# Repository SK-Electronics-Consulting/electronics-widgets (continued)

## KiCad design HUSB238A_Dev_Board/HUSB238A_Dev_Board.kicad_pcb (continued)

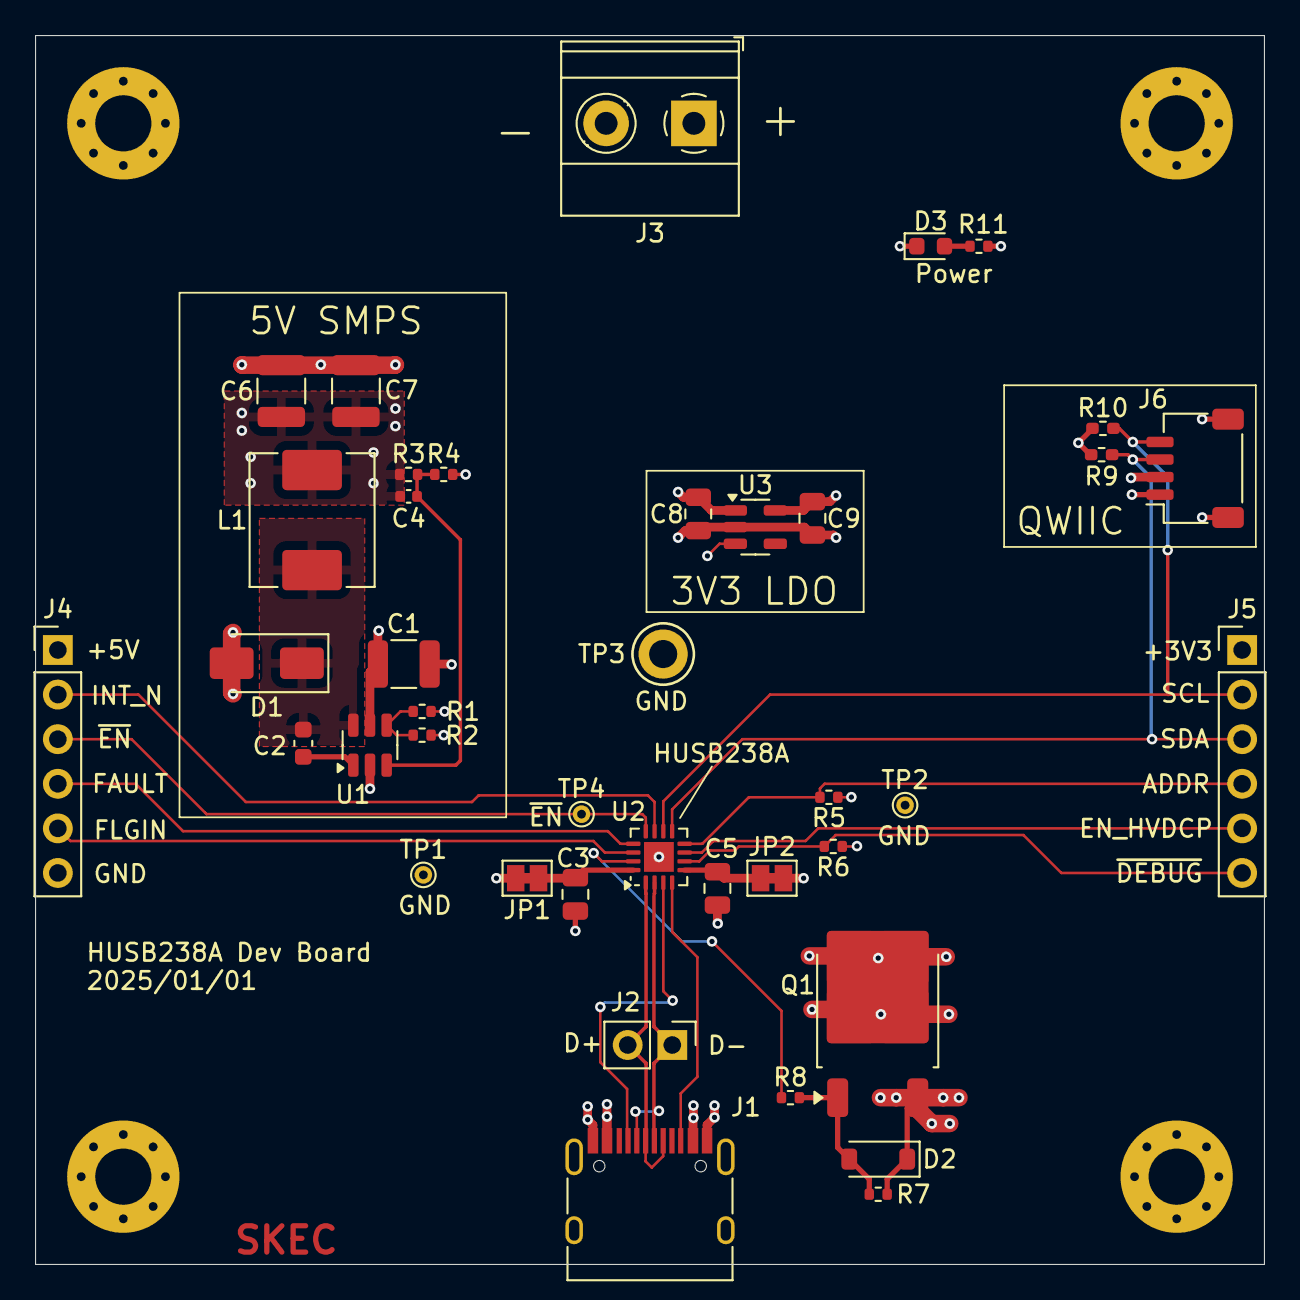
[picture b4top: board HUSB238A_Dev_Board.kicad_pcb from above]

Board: 4 copper layers, 70.0 x 70.0 mm, 44 parts (0 on the bottom side), 27 nets.

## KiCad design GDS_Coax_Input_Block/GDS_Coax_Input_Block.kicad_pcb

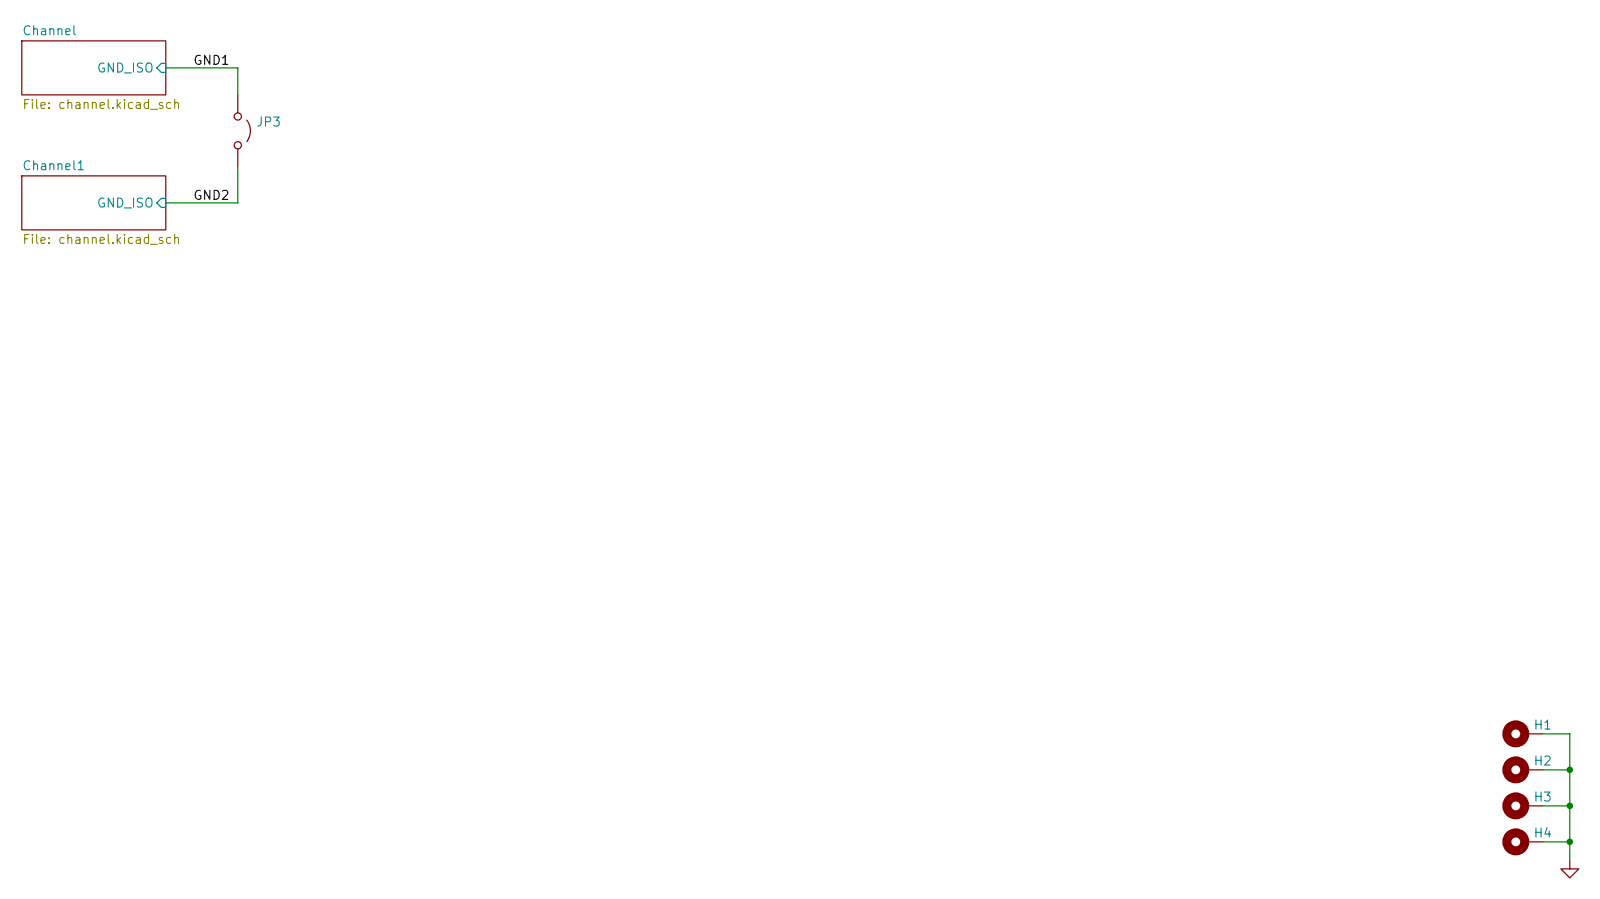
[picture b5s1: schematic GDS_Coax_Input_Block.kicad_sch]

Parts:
H1, H2, H3, H4: MountingHole_Pad; MountingHole_3.2mm_M3_Pad_Via
JP3: Jumper_2_Open; PinHeader_1x02_P2.54mm_Vertical

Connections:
/GND1: JP3.1 (A); also elsewhere on the board
/GND2: JP3.2 (B); also elsewhere on the board
GND: H1.1, H2.1, H3.1, H4.1

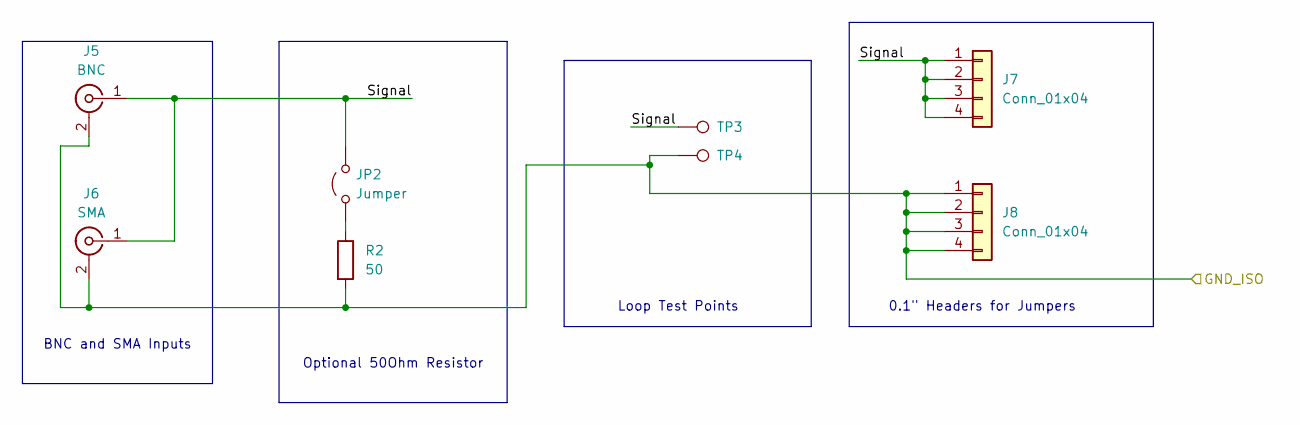
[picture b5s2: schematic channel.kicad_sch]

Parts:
J5: BNC; BNC_TEConnectivity_1478204_Vertical
J6: SMA; SMA_Amphenol_132134-11_Vertical
J7, J8: Conn_01x04; PinHeader_1x04_P2.54mm_Vertical
JP2: Jumper; SolderJumper-2_P2.54mm_Bridged
R2: 50; R_0603_1608Metric_Pad0.98x0.95mm_HandSolder
TP3, TP4: TestPoint; TestPoint_Keystone_5010-5014_Multipurpose

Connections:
/Channel/Signal: J5.1 (In), J6.1 (In), J7.1, J7.2, J7.3, J7.4, JP2.2 (B), TP3.1
/GND1: J5.2 (Ext), J6.2 (Ext), J8.1, J8.2, J8.3, J8.4, R2.2, TP4.1; also elsewhere on the board
unnamed: JP2.1 (A), R2.1

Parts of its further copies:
J1: BNC; BNC_TEConnectivity_1478204_Vertical
J2: SMA; SMA_Amphenol_132134-11_Vertical
J3, J4: Conn_01x04; PinHeader_1x04_P2.54mm_Vertical
JP1: Jumper; SolderJumper-2_P2.54mm_Bridged
R1: 50; R_0603_1608Metric_Pad0.98x0.95mm_HandSolder
TP1, TP2: TestPoint; TestPoint_Keystone_5010-5014_Multipurpose

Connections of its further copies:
/Channel1/Signal: J1.1 (In), J2.1 (In), J3.1, J3.2, J3.3, J3.4, JP1.2 (B), TP1.1
/GND2: J1.2 (Ext), J2.2 (Ext), J4.1, J4.2, J4.3, J4.4, R1.2, TP2.1; also elsewhere on the board
unnamed: JP1.1 (A), R1.1

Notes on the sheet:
Loop Test Points
BNC and SMA Inputs
0.1" Headers for Jumpers
Optional 50Ohm Resistor

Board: 4 copper layers, 21 parts (0 on the bottom side), 7 nets, no tracks yet.

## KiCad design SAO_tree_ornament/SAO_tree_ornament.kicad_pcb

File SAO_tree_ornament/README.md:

# SAO Tree Ornament

This board allows you to easily hang and display your SAOs on a tree or other decoration.  It provides power via USB-PB and optionally a small MCU to drive the pins.

## Features

* USB-PD Power entry.  Negotiates for up to <20V@3.25A> (The USB-PD 3.0 65W profile).
* Distributes the high voltage out to other ornaments
* Converts the high voltage down to 3.3V for the SAO
* An MCU can drive the I2C and the GPIO pins if the SAO needs it.

## TODO

* Test and characterize the current capability of the buck converter

## Next Version Notes

1. Add SOME LEDs to the front of the board to optionally backlight the SAO
2. Add some art to the front of the board
3. Figure out a more efficient counterbalance solution. I underestimated the weight of some of the SAO. A 5mm dowel to bind to the branch might be an option.
4. Might need to move the 2-pin connectors so they don't interfere with the SAO connector.  TBD
5. Reduce 6-pin connector hole sizes. A 0.2mm diameter drop is a good start.  Probably will end up at 0.3mm reduction overall.

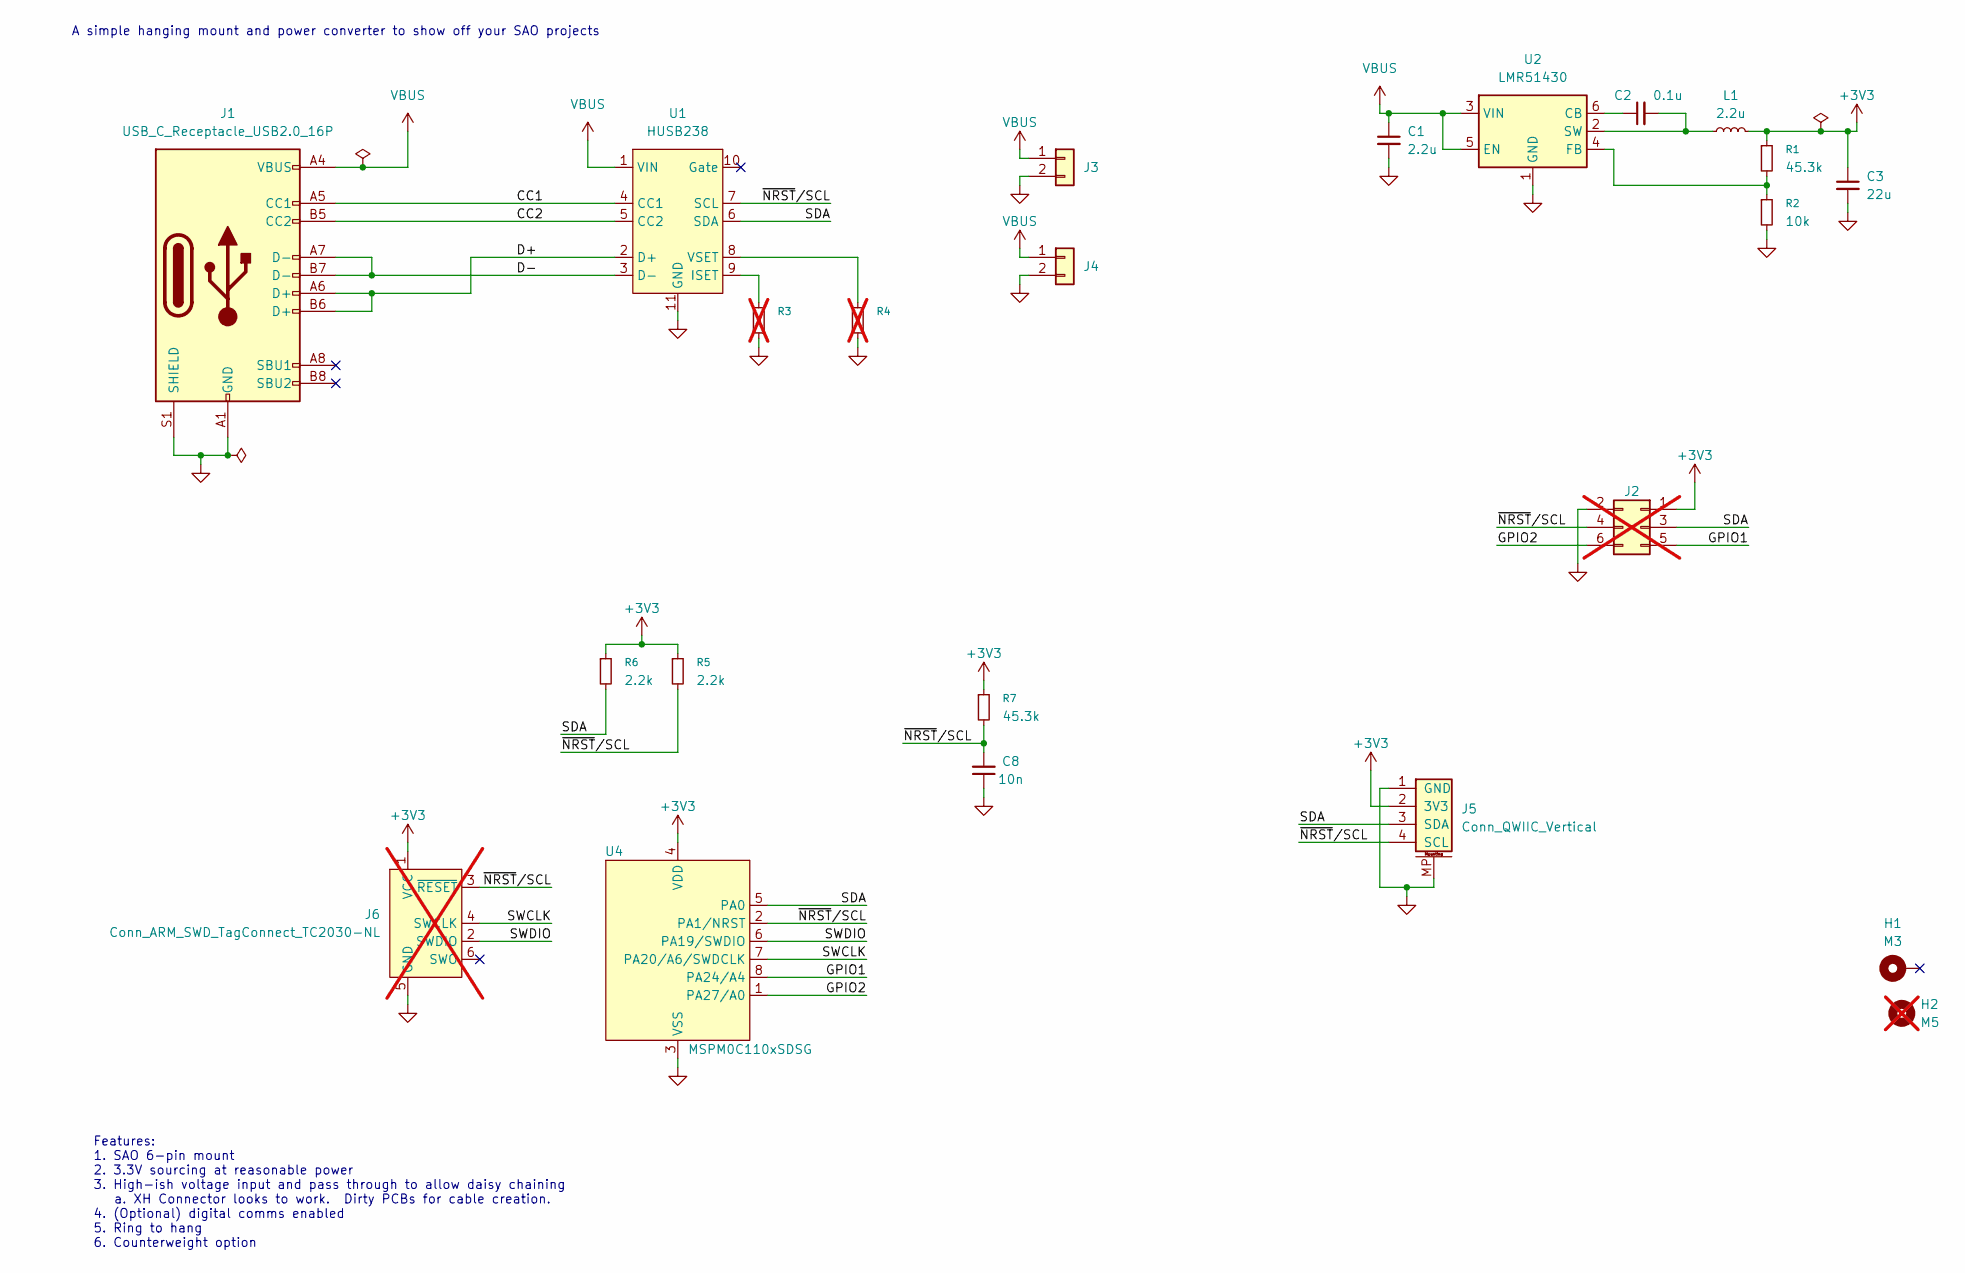
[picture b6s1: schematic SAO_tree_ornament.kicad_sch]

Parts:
C1: 2.2u; C_0603_1608Metric; MPN CL10A225KB8NNNC; JLCPCB Part No. C913904
C2: 0.1u; C_0402_1005Metric; MPN CC0402KRX5R9BB104; JLCPCB Part No. C105882
C3: 22u; C_0603_1608Metric; MPN CL10A226MO7JZNC; JLCPCB Part No. C2762594
C8: 10n; C_0402_1005Metric; MPN CC0402KRX7R0BB103; JLCPCB Part No. C527014
H1: M3; Nut_M3_Sinhoo_SMTSO30xxyyy; MPN SMTSO3050CTJ; JLCPCB Part No. C2915636
H2: M5; MountingHole_5.3mm_M5; not fitted
J1: USB_C_Receptacle_USB2.0_16P; USB_C_Receptacle_G-Switch_GT-USB-7051x; MPN GT-USB-7051A; JLCPCB Part No. C2843970
J2: Conn_02x03_Odd_Even; PinSocket_2x03_P2.54mm_Vertical; not fitted
J3, J4: Conn_01x02; JST_XH_B2B-XH-AM_1x02_P2.50mm_Vertical; MPN B2B-XH-AM(LF)(SN); JLCPCB Part No. C161869
J5: Conn_QWIIC_Vertical; JST_SH_BM04B-SRSS-TB_1x04-1MP_P1.00mm_Vertical; MPN BM04B-SRSS-TBT(LF)(SN); Digi-Key 455-BM04B-SRSS-TBTCT-ND
J6: Conn_ARM_SWD_TagConnect_TC2030-NL; Tag-Connect_TC2030-IDC-NL_2x03_P1.27mm_Vertical; not fitted
L1: 2.2u; L_Changjiang_FXL0420; MPN FXL0420-2R2-M; JLCPCB Part No. C167206
R1, R7: 45.3k; R_0402_1005Metric; MPN RC0402FR-0745K3L; JLCPCB Part No. C137977
R2: 10k; R_0402_1005Metric; MPN RC0402FR-0710KL; JLCPCB Part No. C60490
R3, R4: R_Small; R_0402_1005Metric; not fitted
R5, R6: 2.2k; R_0402_1005Metric; MPN RC0402FR-072K2L; JLCPCB Part No. C114762
U1: HUSB238; DFN-10-1EP_3x3mm_P0.5mm_EP1.65x2.38mm_ThermalVias; JLCPCB Part No. C7471904
U2: LMR51430; SOT-23-6; MPN LMR51430YFDDCR; JLCPCB Part No. C5219261
U4: MSPM0C110xSDSG; WSON-8-1EP_2x2mm_P0.5mm_EP0.9x1.6mm_ThermalVias; MPN MSPM0C1104SDSGR; JLCPCB Part No. C35105978

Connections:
+3V3: C3.1, J2.1, J5.2 (3V3), J6.1 (VCC), L1.2, R1.1, R5.1, R6.1, R7.1, U4.4 (VDD)
/CC1: J1.A5 (CC1), U1.4 (CC1)
/CC2: J1.B5 (CC2), U1.5 (CC2)
/D+: J1.A6 (D+), J1.B6 (D+), U1.2 (D+)
/D-: J1.A7 (D-), J1.B7 (D-), U1.3 (D-)
/GPIO1: J2.5, U4.8 (PA24/A4)
/GPIO2: J2.6, U4.1 (PA27/A0)
/SDA: J2.3, J5.3 (SDA), R6.2, U1.6 (SDA), U4.5 (PA0)
/SWCLK: J6.4 (SWCLK), U4.7 (PA20/A6/SWDCLK)
/SWDIO: J6.2 (SWDIO), U4.6 (PA19/SWDIO)
/~NRST/SCL: C8.2, J2.4, J5.4 (SCL), J6.3 (~RESET), R5.2, R7.2, U1.7 (SCL), U4.2 (PA1/NRST)
GND: C1.2, C3.2, C8.1, J1.A1 (GND), J1.A12 (GND), J1.B1 (GND), J1.B12 (GND), J1.S1 (SHIELD), J2.2, J3.2, J4.2, J5.1 (GND), J5.MP, J6.5 (GND), R2.2, R3.2, R4.2, U1.11 (GND), U2.1 (GND), U4.3 (VSS), U4.9 (Thermal)
unnamed: R3.1, U1.9 (ISET)
unnamed: R4.1, U1.8 (VSET)
unnamed: C2.1, U2.6 (CB)
unnamed: R1.2, R2.1, U2.4 (FB)
unnamed: C2.2, L1.1, U2.2 (SW)
VBUS: C1.1, J1.A4 (VBUS), J1.A9 (VBUS), J1.B4 (VBUS), J1.B9 (VBUS), J3.1, J4.1, U1.1 (VIN), U2.3 (VIN), U2.5 (EN)

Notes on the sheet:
A simple hanging mount and power converter to show off your SAO projects
Features: 1. SAO 6-pin mount 2. 3.3V sourcing at reasonable power 3. High-ish voltage input and pass through to allow daisy chaining a. XH Connector looks to work. Dirty PCBs for cable creation. 4. (Optional) digital comms enabled 5. Ring to hang 6. Counterweight option

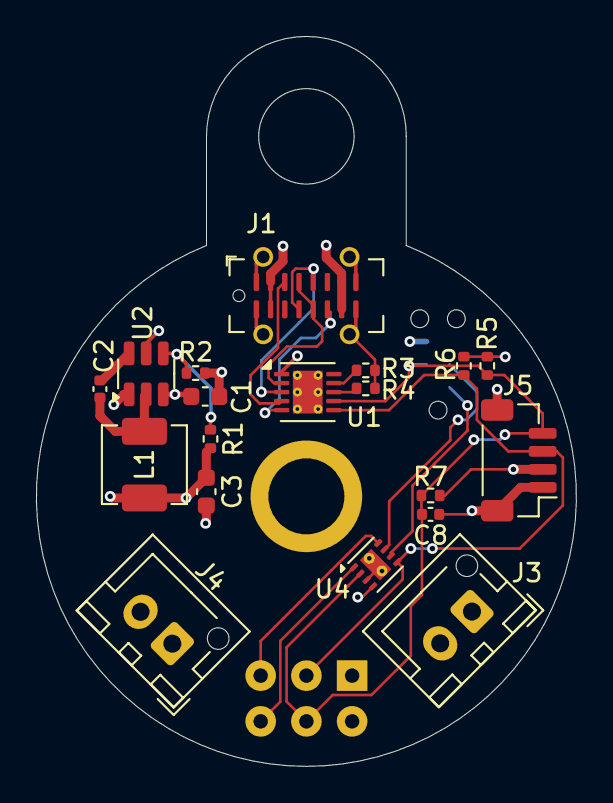
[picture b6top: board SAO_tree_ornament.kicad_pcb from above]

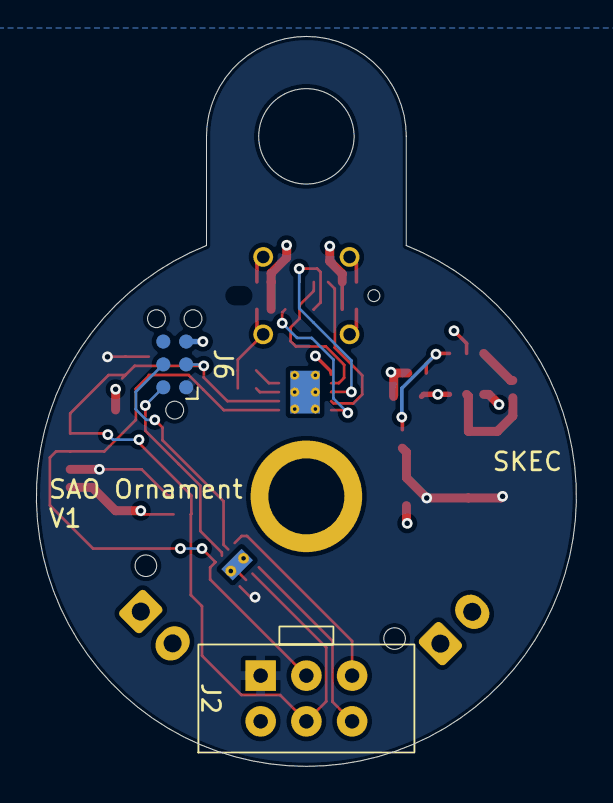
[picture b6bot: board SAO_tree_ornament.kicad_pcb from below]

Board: 4 copper layers, 30.0 x 40.5 mm, 23 parts (2 on the bottom side), 18 nets.

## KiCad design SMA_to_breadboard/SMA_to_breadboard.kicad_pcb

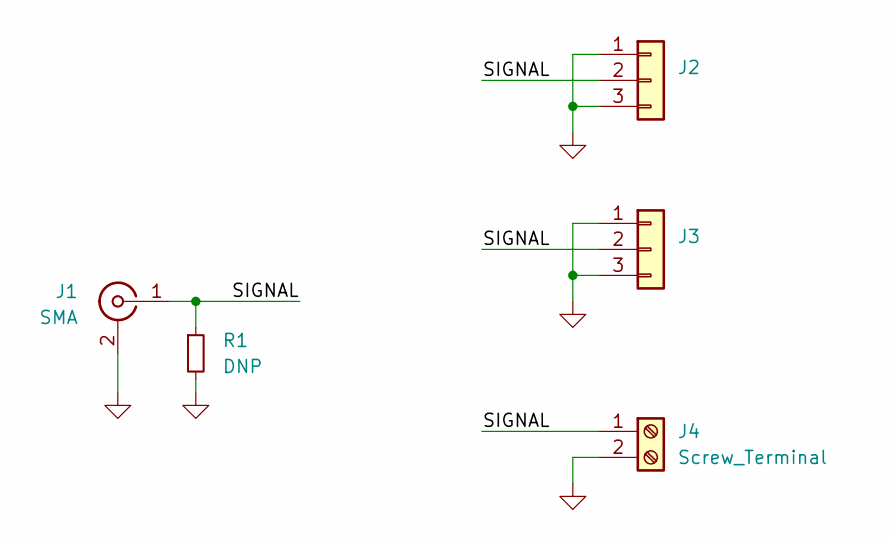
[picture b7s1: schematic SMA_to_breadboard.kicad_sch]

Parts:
J1: SMA; SMA_Samtec_SMA-J-P-H-ST-EM1_EdgeMount
J2, J3: Conn_01x03; PinHeader_1x03_P2.54mm_Vertical
J4: Screw_Terminal; TerminalBlock_Xinya_XY308-2.54-2P_1x02_P2.54mm_Horizontal
R1: DNP; R_0603_1608Metric_Pad0.98x0.95mm_HandSolder

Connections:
/SIGNAL: J1.1 (In), J2.2, J3.2, J4.1, R1.1
GND: J1.2 (Ext), J2.1, J2.3, J3.1, J3.3, J4.2, R1.2

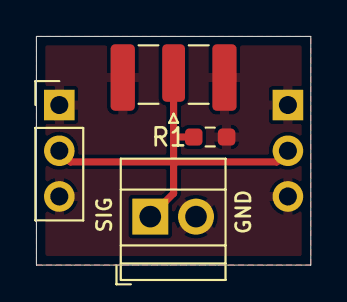
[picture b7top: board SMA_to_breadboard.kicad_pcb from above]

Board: 2 copper layers, 15.2 x 12.7 mm, 5 parts (1 on the bottom side), 2 nets.

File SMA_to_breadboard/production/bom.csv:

Designator,Footprint,Quantity,Value,LCSC Part #
J1,SMA_Samtec_SMA-J-P-H-ST-EM1_EdgeMount,1,SMA,
"J2, J3",PinHeader_1x03_P2.54mm_Vertical,2,Conn_01x03,
J4,TerminalBlock_Xinya_XY308-2.54-2P_1x02_P2.54mm_Horizontal,1,Screw_Terminal,
R1,0603,1,DNP,

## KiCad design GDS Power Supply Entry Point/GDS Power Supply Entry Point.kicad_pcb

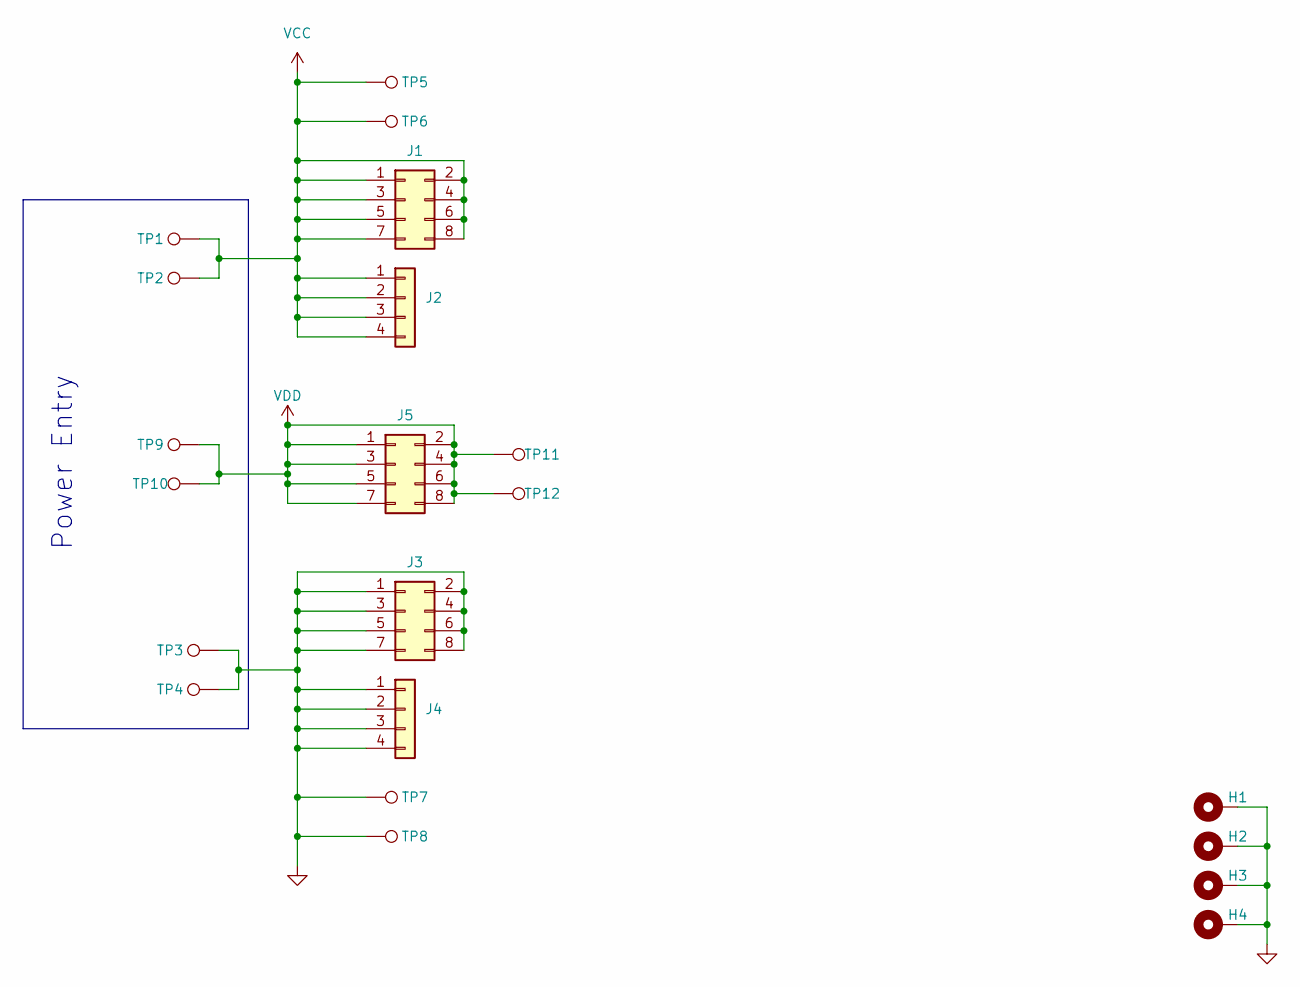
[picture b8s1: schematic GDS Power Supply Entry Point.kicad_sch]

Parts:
H1, H2, H3, H4: MountingHole_Pad; MountingHole_3.2mm_M3_Pad_Via
J1, J3, J5: Conn_01x04; PinHeader_2x04_P2.54mm_Vertical
J2, J4: Conn_01x04; PinSocket_1x04_P2.54mm_Vertical
TP1, TP2, TP3, TP4, TP5, TP6, TP7, TP8, TP9, TP10, TP11, TP12: TestPoint; TestPoint_Keystone_5010-5014_Multipurpose

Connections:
GND: H1.1, H2.1, H3.1, H4.1, J3.1, J3.2, J3.3, J3.4, J3.5, J3.6, J3.7, J3.8, J4.1, J4.2, J4.3, J4.4, TP3.1, TP4.1, TP7.1, TP8.1
VCC: J1.1, J1.2, J1.3, J1.4, J1.5, J1.6, J1.7, J1.8, J2.1, J2.2, J2.3, J2.4, TP1.1, TP2.1, TP5.1, TP6.1
VDD: J5.1, J5.2, J5.3, J5.4, J5.5, J5.6, J5.7, J5.8, TP9.1, TP10.1, TP11.1, TP12.1

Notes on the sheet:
Power Entry

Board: 4 copper layers, 21 parts (0 on the bottom side), 3 nets, no tracks yet.

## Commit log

2023-08-10 "Initial commit of empty project and git-specific files"
2023-08-14 V1 PCB.
2023-08-15 Reorg Repo to be more general
2023-08-15 Add Breadboard Power Supply Adapter
2023-08-15 Add V1 of REF33xx board
2023-08-15 Add Breadboard PSU V2 thoughts.
2023-08-16 Made V2 Breadboard Power Supply Adapter
    Removed several redundant test points. Re-using the Banana jack pads is
    sufficient for Keystone and wires.
    Added 3-pin regulator footprint, along with output pin. Could be used
    for secondary voltage supply or reference regulator.
2023-08-16 Update README for Breadboard Power Supply Adapter
2023-09-07 Update gitignore to suppress kicad's lock files
2023-09-07 Update footprint to include SMT pads.
    This was done in a way where the backside also has SMT "pads". This is
    not ideal, but works to clean up the design overall.
2023-09-07 Add ECO comments from V1 fab and build.
2023-09-08 Consolidate 10-pin connection on schematic
2023-09-08 Fix the footprint for JLink and add comments
    The footprint used for the 20-pin connector ended up being backwards wrt
    Jlink connection. Using the PinSocket family fixes this without having
    to draw a custom connector.
    Added comments and meta-data to the schematic
2023-09-08 Update the 10-pin footprint with solid models
2023-09-08 Re-layout PCB
    * Changed to 4-layer board.
    * Centered SWD connector
    * Moved all non-user components to back-side
    * Moved Jlink Connector in, instead of expanding board
2023-09-08 Fix some DRC, tidy docs, and move a few traces.
    Cleaned up and tidied the fabrication layer.
    Also, decided to make the Front layer trace-free for aesthetics. Did so
    with via-in-pad for the LEDs. This should be fine because this is being
    hand soldered.
2023-09-08 Finalize V2 of Jlink adapter
    Cleaned up more DRC errors
2023-09-08 Jlink adapter V2 ordered
2023-09-08 Update READMEs
2023-09-08 Generated
2023-09-08 Remove docs in wrong place
2023-11-13 Board first commit
2023-11-14 V1.0 of 2032 PCB
2024-02-28 Added v1 of Raspberry Pi Power Adapter
2024-03-31 V3 of the Jlink board
2024-04-10 Add feedback from V3 build, and update README
2024-04-10 Update Action condition and uploading
2024-04-10 Update Jlink Adapter README
2024-04-10 Update YML
2024-04-10 Update Jlink to clear ERC issues
2024-04-10 Remove DRC exclusion
2024-04-10 Add submodule and fix PCB
2024-04-10 Remove possible issue component to clear up KiCAD DRC
2024-09-02 Update gitignore for KiCAD v8
2024-09-02 Release V1 of Diff Amp for Breadboard PCB
2024-09-03 Remove Production Backups directory and associated file, and update gitignore
2024-09-03 Release V1 of the SMA to Breadboard PCB
2024-11-09 Add V1 of the QWIIC-CAN to Saleae adapter PCB
2024-12-27 Add QWIIC_CAN README
2024-12-27 Update root README
2025-04-08 V2 QWIIC board
2025-06-04 Add features and minor improvements from V4
    * Add Custom Segger Adapter
    * Add a 5V tap off point
    * Add a reset button for the MCU
    * Remove Jumpers
    * Swapped the Inner Plane to supply Vtref, rather than 5V, as 5V goes to fewer places.
2025-06-04 Update github actions workflow
2025-06-04 Extend pad length of SWD Connector by 0.5mm
2025-06-04 Reduce Jlink connector hole size 0.8mm->0.7mm
2025-06-04 Update KiBot YAML and Fix minor DRC error
2025-06-04 kibot yaml
2025-06-04 kibot
2025-06-04 Update library submodule
2025-06-04 Update KiBot Yaml to add filters
2025-06-04 Capture Ideas post v2 and including GDS mount
2025-06-19 Release GND breakout PCB
    Tiny little PCB to work with the Gridfinity breadboard adapter. Meant to give a sturdy ground grabbing point for o-scope clips and whatnot.
2025-06-19 Add README
2025-06-19 V3 of Saleae Adapter
    Added the other 4 channels and a mounting hole for the Gridfinity holder
2025-06-25 V1 of GDS Power Entry Point
2025-06-25 Release V1 of SAO Tree Ornament
2025-06-27 Add Kibot workflow
2025-07-09 Update Main README
2025-07-14 Update README to remove todo that the MCU is programmable
2025-07-14 Update READMEs with next version notes
2025-07-16 Update submodule reference
2025-07-16 Update SAO Connector on badge
2025-09-03 Add finding of boot loop
2025-09-03 USB Hub Schematic Complete
2025-09-06 Fix bus naming to use all four channels
2025-09-07 USB Hub Board as order submitted on 9/6
    This might get rejected by JLC for via sizes.
2025-11-12 Update to USB Hub to use symbol in library. Probably some other changes as well
2025-11-12 Snapshot of GDS Coax input block
2025-11-12 Add ideas for next version in README
2025-11-12 Release V1 of the BOB PCB
2025-11-12 Add HUSB238A dev board V1
    TODO: Add order of operations info for turning on power. (Found in datasheets, but not very clearly explained)
2026-01-15 Christmas Tree Timer Initial commit
2026-01-15 CR2032 Checkpoint, changing computers
2026-03-06 Finalized V2.
2026-03-06 Pixelblaze Battery Backpack V1 Release
    Forgot to put Silkscreen text on there.
2026-03-06 Checkpoint, changing computers
2026-03-06 Add 3x channels of spare LEDs for general breadboard use, add silkscreen. Ordered this version
2026-03-06 V2 complete, ready for review and polish
